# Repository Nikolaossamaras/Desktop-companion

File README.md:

# Desktop-companion
>A desktop robot that keeps you company , provides liveliness to your desk and keeps you energised to work all day

# Why i build it
## i wanted to test my skills in pcb making(it was my first time , so feel free to edit the files) and i though that having a small robot on your desk will be super cool

---

# What is it

It's a small robot roughly 80x85x40 mm that just keeps you company reacts to your touch and to any movement that happens on the desk

---

# What you need :

- the pcb , that you can order from pcbway or JLCPCB
- if you dont want the pcb you can buy the modules by them selves
- check the BOM in the files to know exactly what you need

|touch module x1|$3.35 for 10 pieces |
|mpu6050 x1|$4.62 per piece|
|Wemos D1 Mini ESP32 x1|$6.25  per piece |
|Screen Module ST7735 SPI Serial 51|5.08$ per piece|
|total| roughly 20$(idk if the pcb costs more or less , i havent tried)|

# Project preview

## Full companion Design

## Schematic 

## Pcb

# Firmware 

the Firmware is the code , but i am not sure if it works cause i dont have the parts on me .
The code also may be wrong for the same reason .

## Code
[here](https://github.com/Nikolaossamaras/Desktop-companion/blob/main/desktopcompcode.ino) is the link for the code (as i said earlier the code does not fully 100% work)

## Assembly

I have made a plan of assembly not 100% sure if it will work (it should though) . You can follow it if you like [here](https://github.com/Nikolaossamaras/Desktop-companion/blob/main/PLAN%20for%20desktop%20companion.(assembl.txt ) it is

# Credits

- [Fusion 360](https://fusion-360.en.uptodown.com/windows) – 3D Case Designing
- [Hack Club](https://hackclub.com/) – For giving me the chance to embark on this project
- [kicad](https://www.kicad.org/download/) – PCB and Schematic design
- [Maker_science](https://www.youtube.com/@Maker_science) - The code is borrowed from him as well as the Idea

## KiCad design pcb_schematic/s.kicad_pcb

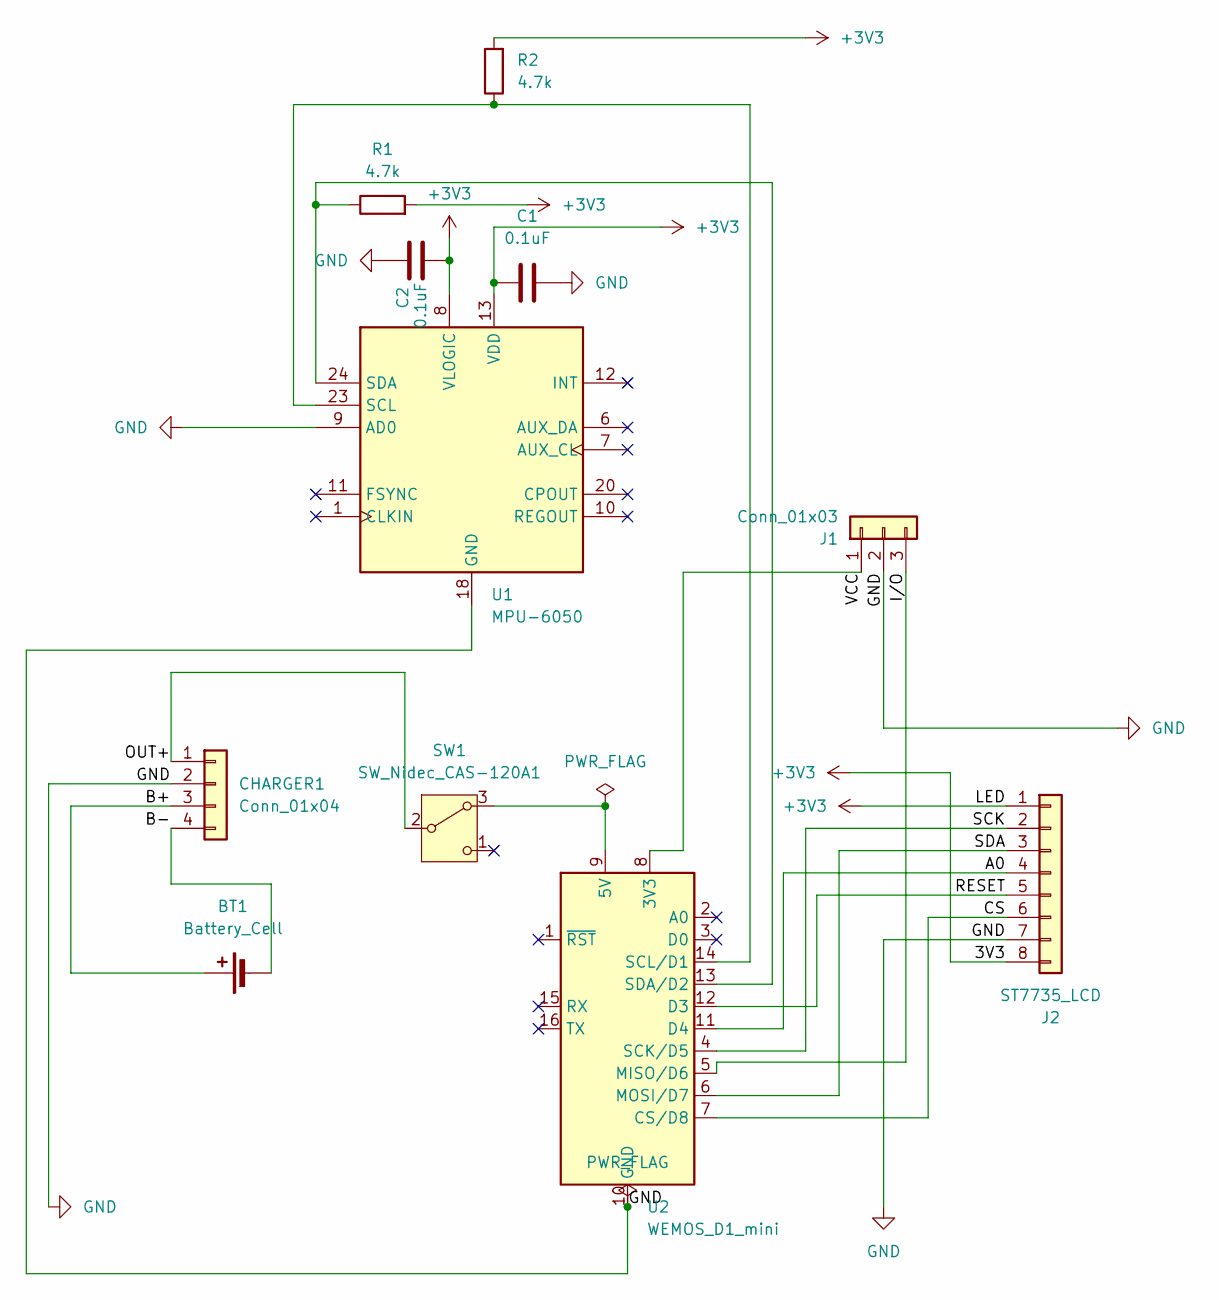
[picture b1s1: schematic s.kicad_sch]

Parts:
BT1: Battery_Cell; JST_PH_S2B-PH-K_1x02_P2.00mm_Horizontal
C1, C2: 0.1uF; C_0805_2012Metric
CHARGER1: Conn_01x04; PinHeader_1x04_P2.54mm_Horizontal
J1: Conn_01x03; PinHeader_1x03_P2.54mm_Horizontal
J2: ST7735_LCD; PinHeader_1x08_P2.54mm_Horizontal
R1, R2: 4.7k; R_0805_2012Metric
SW1: SW_Nidec_CAS-120A1; Nidec_Copal_CAS-120A
U1: MPU-6050; InvenSense_QFN-24_4x4mm_P0.5mm
U2: WEMOS_D1_mini; WEMOS_D1_mini_light

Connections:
+3V3: C1.1, C2.2, J2.1, J2.8, R1.2, R2.2, U1.8 (VLOGIC), U1.13 (VDD)
/A0: J2.4, U2.11 (D4)
/B+: BT1.1 (+), CHARGER1.3
/B-: BT1.2 (-), CHARGER1.4
/CS: J2.6, U2.7 (CS/D8)
/I/O: J1.3, U2.5 (MISO/D6)
/OUT+: CHARGER1.1, SW1.2 (B)
/RESET: J2.5, U2.12 (D3)
/SCK: J2.2, U2.4 (SCK/D5)
/SDA: J2.3, U2.6 (MOSI/D7)
/VCC: J1.1, U2.8 (3V3)
GND: C1.2, C2.1, CHARGER1.2, J1.2, J2.7, U1.9 (AD0), U1.18 (GND), U2.10 (GND)
unnamed: SW1.3 (A), U2.9 (5V)
unnamed: R2.1, U1.23 (SCL), U2.14 (SCL/D1)
unnamed: R1.1, U1.24 (SDA), U2.13 (SDA/D2)

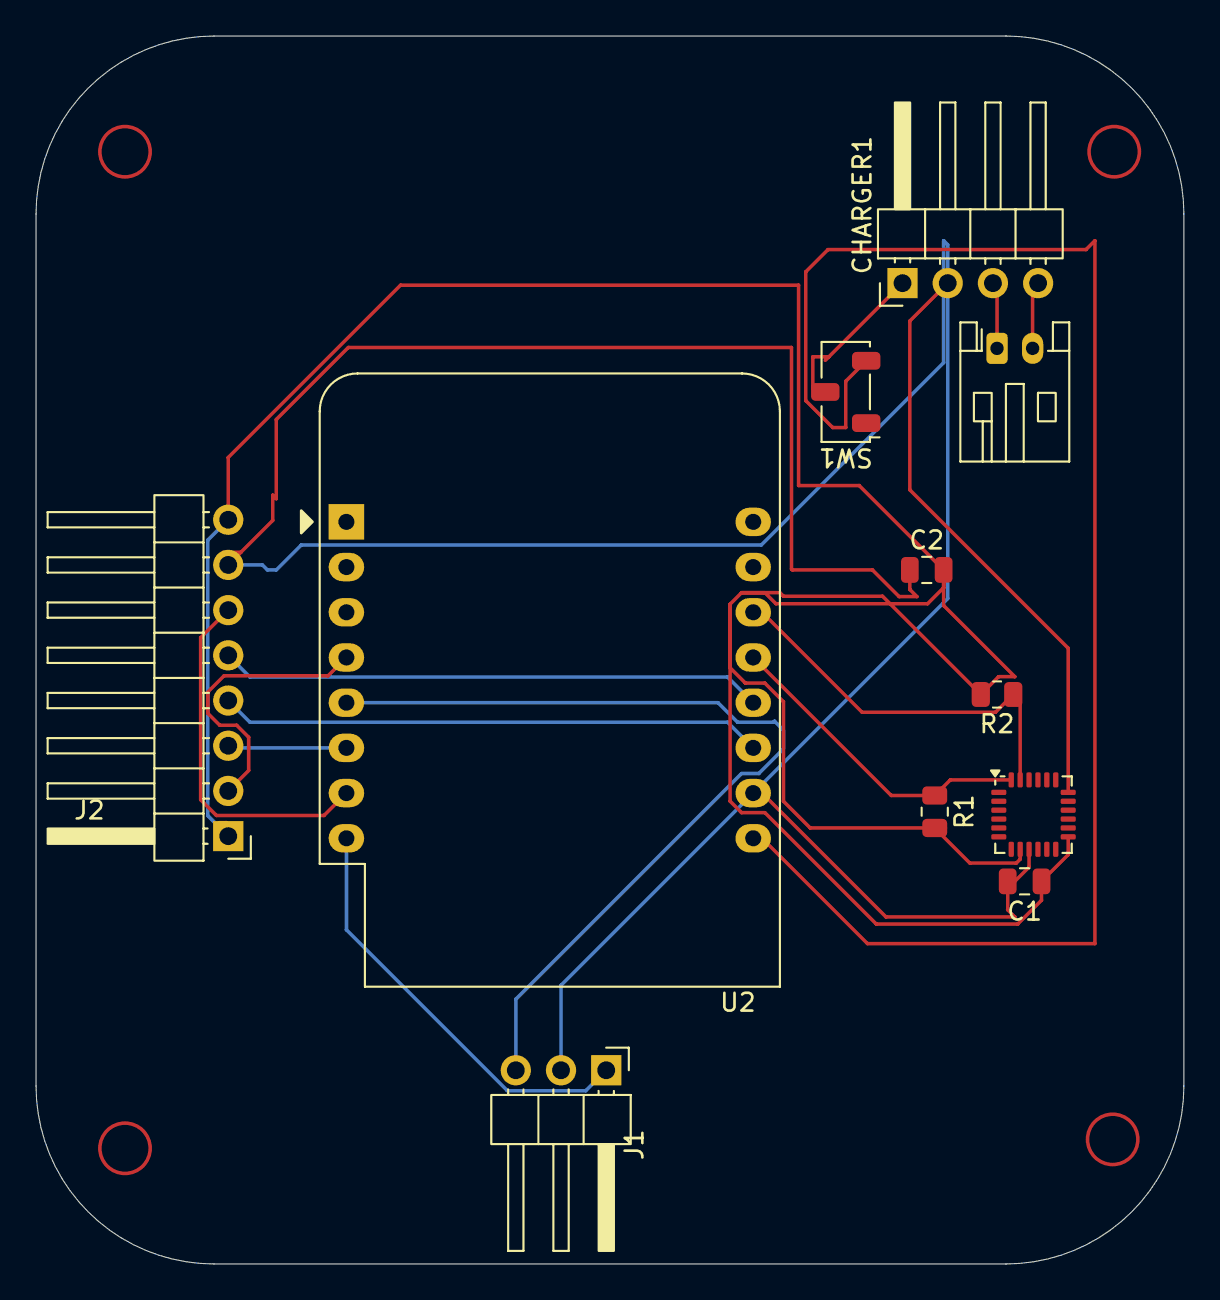
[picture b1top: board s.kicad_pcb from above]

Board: 2 copper layers, 64.5 x 69.0 mm, 11 parts (0 on the bottom side), 15 nets.
